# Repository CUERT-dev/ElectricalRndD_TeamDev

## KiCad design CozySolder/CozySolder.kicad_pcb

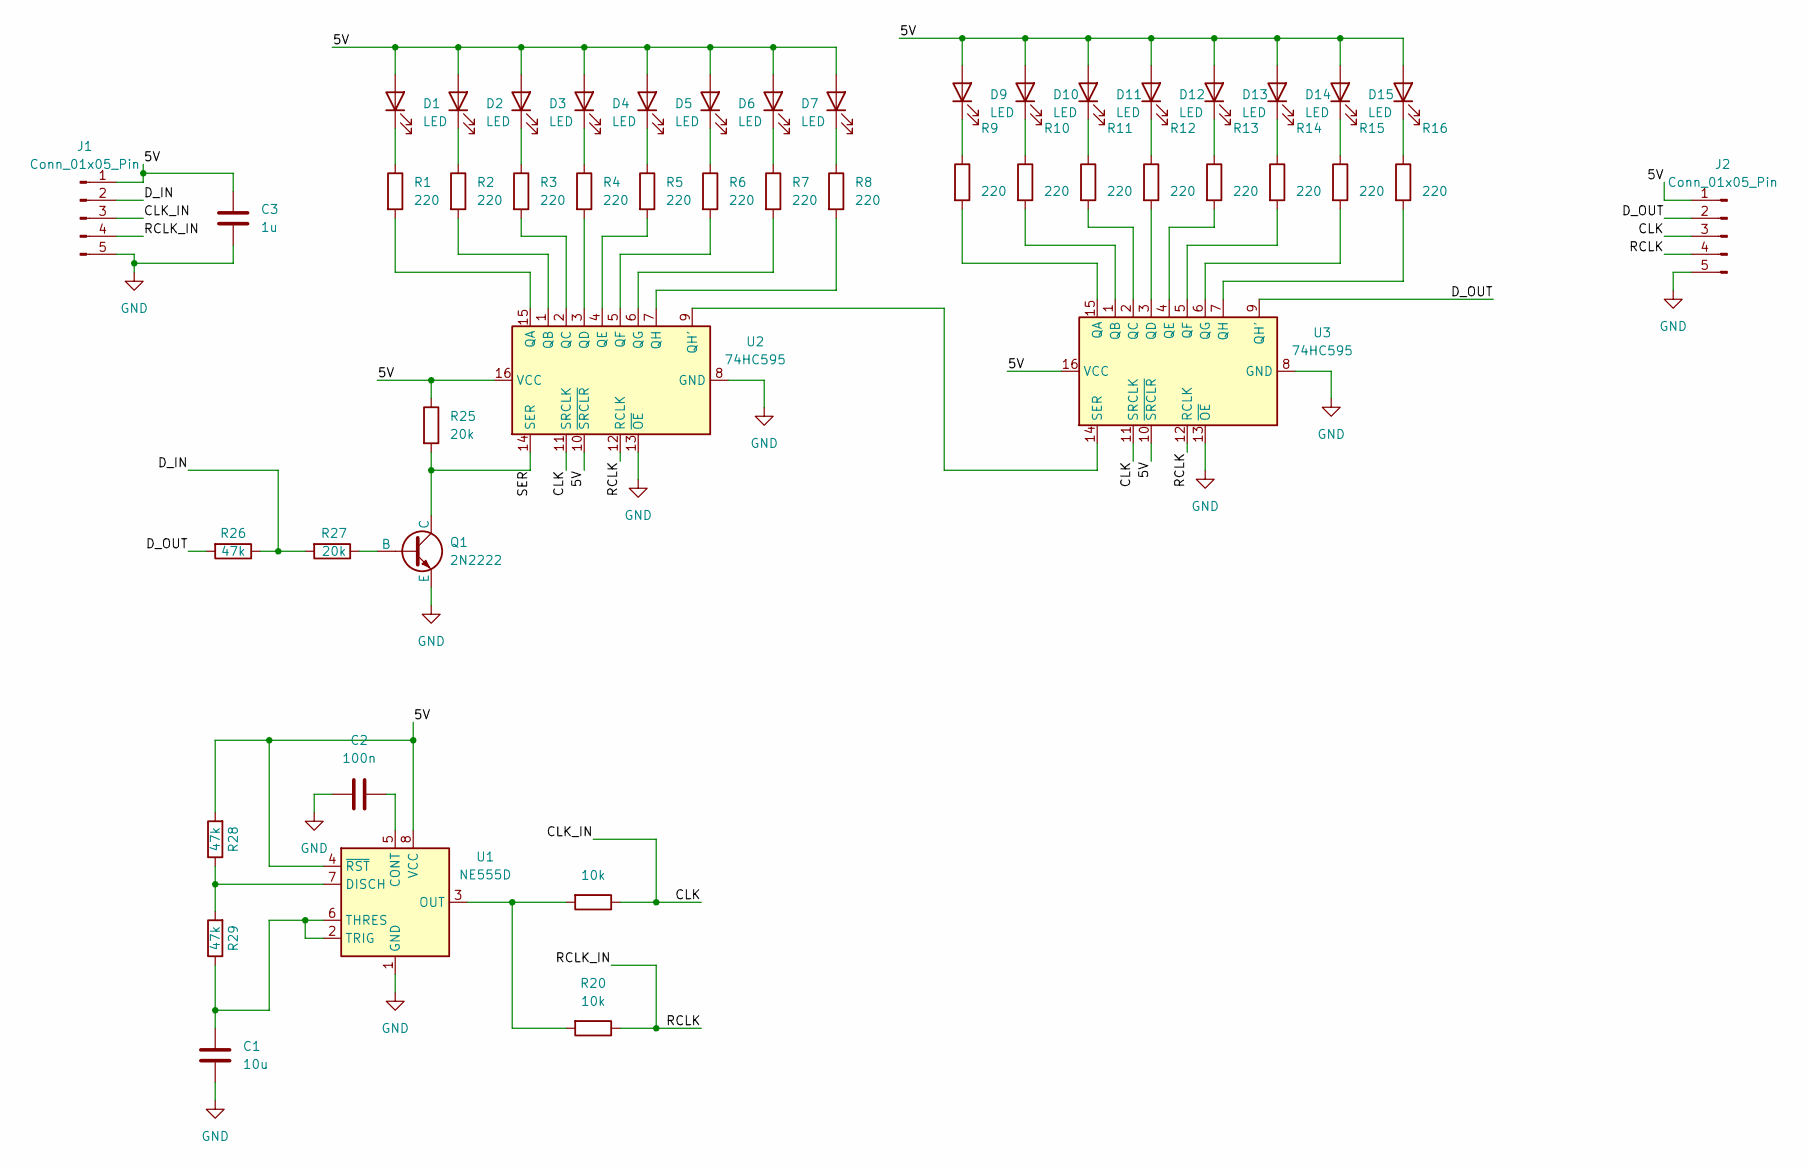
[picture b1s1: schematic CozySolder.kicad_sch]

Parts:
C1: 10u; C_0603_1608Metric_Pad1.08x0.95mm_HandSolder
C2: 100n; C_0603_1608Metric_Pad1.08x0.95mm_HandSolder
C3: 1u; C_0603_1608Metric_Pad1.08x0.95mm_HandSolder
D1, D2, D3, D4, D5, D6, D7, D8, D9, D10, D11, D12, D13, D14, D15, D16: LED; LED_0603_1608Metric_Pad1.05x0.95mm_HandSolder
J1, J2: Conn_01x05_Pin; SolderWirePad_1x01_SMD_2x4mm
Q1: 2N2222; SOT-23_Handsoldering
R1, R2, R3, R4, R5, R6, R7, R8, R9, R10, R11, R12, R13, R14, R15, R16: 220; R_0603_1608Metric_Pad0.98x0.95mm_HandSolder
R17, R20: 10k; R_0603_1608Metric_Pad0.98x0.95mm_HandSolder
R25, R27: 20k; R_0603_1608Metric_Pad0.98x0.95mm_HandSolder
R26, R28, R29: 47k; R_0603_1608Metric_Pad0.98x0.95mm_HandSolder
U1: NE555D; SOIC-8_3.9x4.9mm_P1.27mm
U2, U3: 74HC595; SOIC-16_3.9x9.9mm_P1.27mm

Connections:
/5V: C3.2, D1.2 (A), D2.2 (A), D3.2 (A), D4.2 (A), D5.2 (A), D6.2 (A), D7.2 (A), D8.2 (A), D9.2 (A), D10.2 (A), D11.2 (A), D12.2 (A), D13.2 (A), D14.2 (A), D15.2 (A), D16.2 (A), J1.1, J2.1, R25.1, R28.2, U1.4 (~RST), U1.8 (VCC), U2.10 (~SRCLR), U2.16 (VCC), U3.10 (~SRCLR), U3.16 (VCC)
/CLK: J1.3, J2.3, R17.1, U2.11 (SRCLK), U3.11 (SRCLK)
/D_IN: J1.2, R26.1, R27.2
/D_OUT: J2.2, R26.2, U3.9 (QH')
/RCLK: J1.4, J2.4, R20.1, U2.12 (RCLK), U3.12 (RCLK)
/SER: Q1.1 (C), R25.2, U2.14 (SER)
GND: C1.2, C2.2, C3.1, J1.5, J2.5, Q1.3 (E), U1.1 (GND), U2.8 (GND), U2.13 (~OE), U3.8 (GND), U3.13 (~OE)
unnamed: D1.1 (K), R1.1
unnamed: D2.1 (K), R2.1
unnamed: D3.1 (K), R3.1
unnamed: D4.1 (K), R4.1
unnamed: D5.1 (K), R5.1
unnamed: D6.1 (K), R6.1
unnamed: D7.1 (K), R7.1
unnamed: D8.1 (K), R8.1
unnamed: D9.1 (K), R9.1
unnamed: D10.1 (K), R10.1
unnamed: D11.1 (K), R11.1
unnamed: D12.1 (K), R12.1
unnamed: D13.1 (K), R13.1
unnamed: D14.1 (K), R14.1
unnamed: D15.1 (K), R15.1
unnamed: D16.1 (K), R16.1
unnamed: Q1.2 (B), R27.1
unnamed: C2.1, U1.5 (CONT)
unnamed: R28.1, R29.2, U1.7 (DISCH)
unnamed: R17.2, R20.2, U1.3 (OUT)
unnamed: C1.1, R29.1, U1.2 (TRIG), U1.6 (THRES)
unnamed: R1.2, U2.15 (QA)
unnamed: R2.2, U2.1 (QB)
unnamed: R3.2, U2.2 (QC)
unnamed: R4.2, U2.3 (QD)
unnamed: R5.2, U2.4 (QE)
unnamed: R6.2, U2.5 (QF)
unnamed: R7.2, U2.6 (QG)
unnamed: U2.9 (QH'), U3.14 (SER)
unnamed: R8.2, U2.7 (QH)
unnamed: R9.2, U3.15 (QA)
unnamed: R10.2, U3.1 (QB)
unnamed: R11.2, U3.2 (QC)
unnamed: R12.2, U3.3 (QD)
unnamed: R13.2, U3.4 (QE)
unnamed: R14.2, U3.5 (QF)
unnamed: R15.2, U3.6 (QG)
unnamed: R16.2, U3.7 (QH)

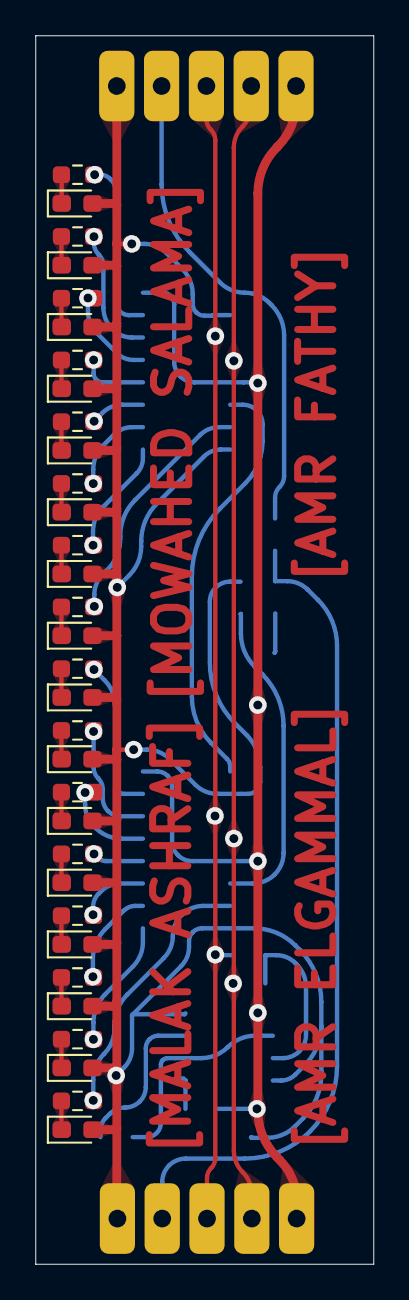
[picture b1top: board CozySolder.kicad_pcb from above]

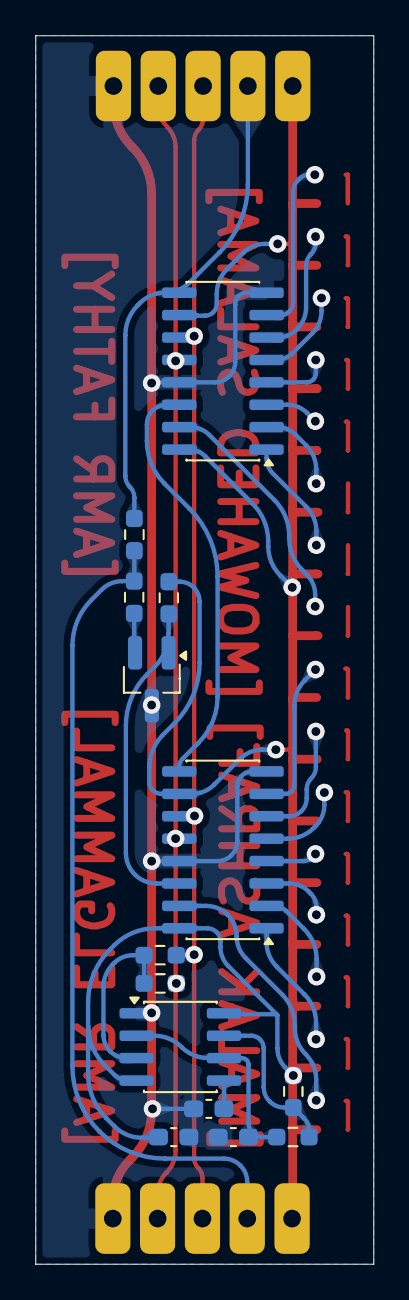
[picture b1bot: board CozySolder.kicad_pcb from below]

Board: 2 copper layers, 19.2 x 69.6 mm, 48 parts (14 on the bottom side), 45 nets.
